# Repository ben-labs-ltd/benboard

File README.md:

# BenBoard

The highly customisable, open source, premium 42 key ergo mechanical keyboard

Show your interest at https://ben-labs.co.uk

## Features

- Reduced layout 42 key split keyboard
- Cherry MX hotswap compatable (any 3 or 5 pin)
- Fully wireless (BLE)
- Month-long battery life with the low power NRF52840
- Out of the box ZMK Support
- Supports [VIK](https://github.com/sadekbaroudi/vik) (on both sides!)
- Unibody case that has been verified to be CNC'able

## Contribution

[ ] TODO

## VIK Certification

| Category                 | Classification          | Response           |
| -----------------------  | ----------------------- | ------------------ |
| FPC connector            | Required                | :heavy_check_mark: |
| Breakout pins            | Recommended             | :x:                |
| Supplies: SPI            | Required                | :heavy_check_mark: |
| Supplies: I2C            | Required                | :heavy_check_mark: |
| I2C on main PCB          | Discouraged             | :x:                |
| I2C pull ups             | Informative             | :x:                |
| Supplies: RGB            | Required                | :heavy_check_mark: |
| Supplies: Extra GPIO 1   | Required                | :heavy_check_mark: (Analogue and Digital) |
| Supplies: Extra GPIO 2   | Required                | :heavy_check_mark: (Analogue and Digital) |

THIS IS A WORK IN PROGRESS, ANY FEATURES LISTED ARE PURELY IN PROGRESS

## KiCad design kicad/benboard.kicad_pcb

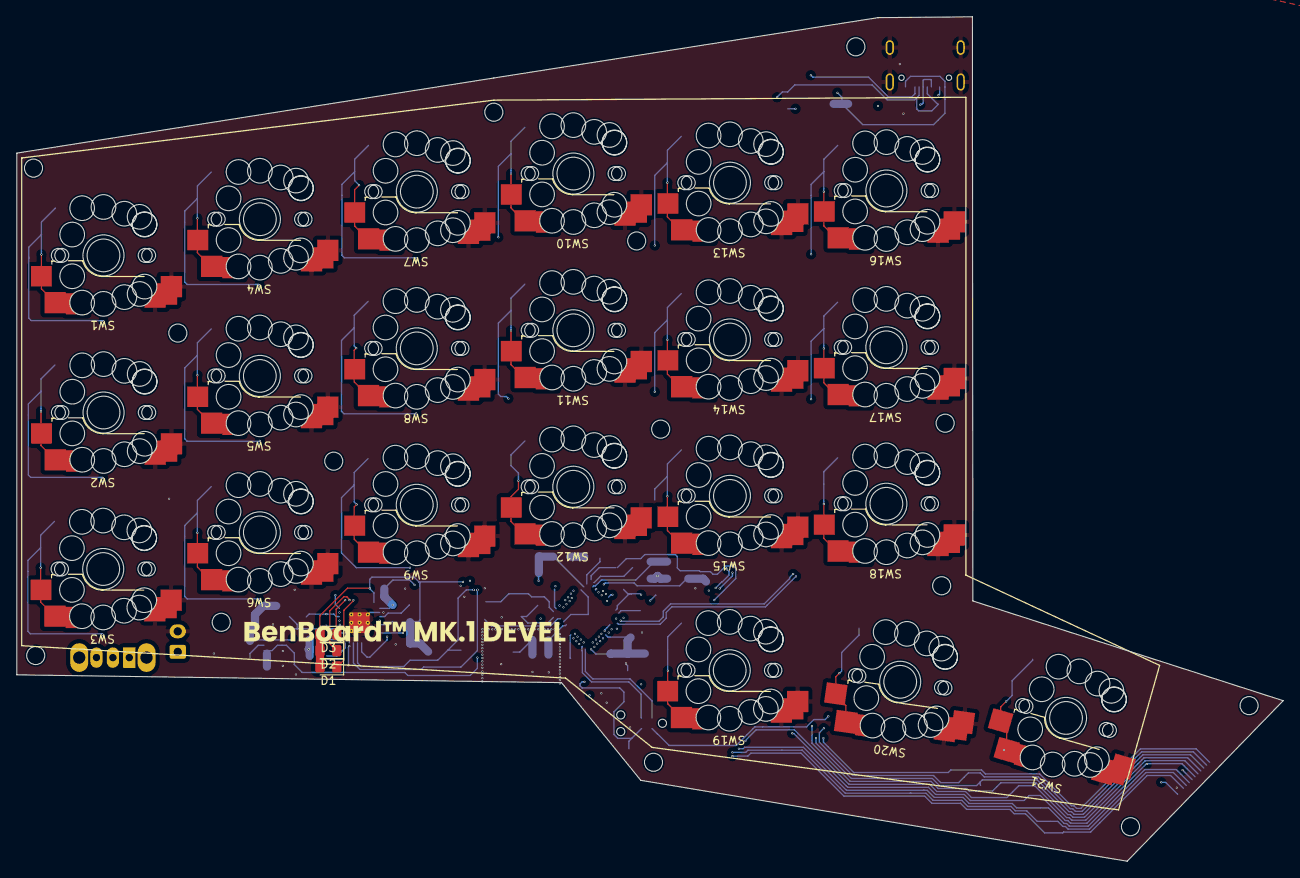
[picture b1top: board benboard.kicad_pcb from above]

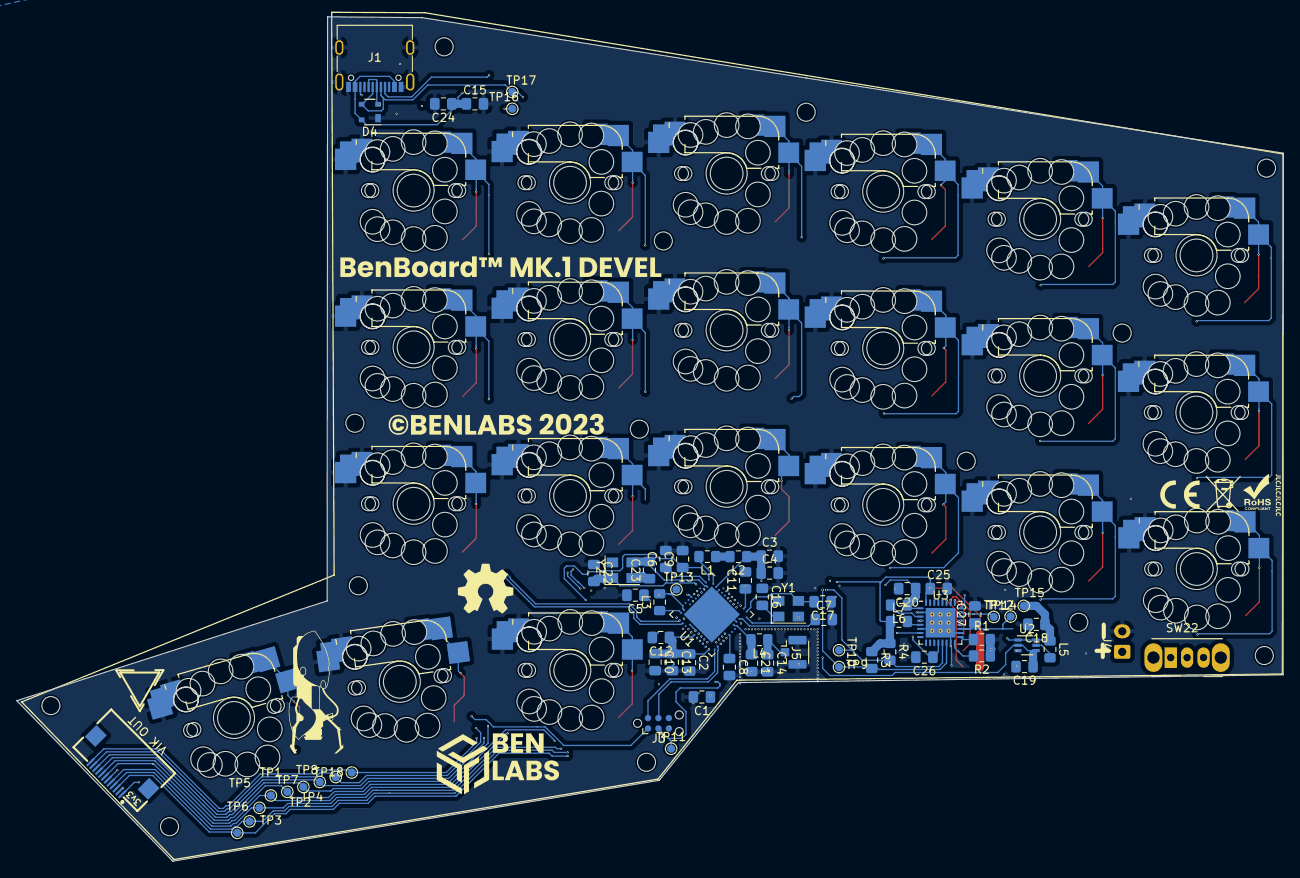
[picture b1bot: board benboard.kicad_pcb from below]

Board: 4 copper layers, 154.2 x 102.9 mm, 92 parts (67 on the bottom side), 70 nets.

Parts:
C1, C3, C13, C15: 1uF; C_0805_2012Metric_Pad1.18x1.45mm_HandSolder
C2, C5, C9: 4.7uF; C_0805_2012Metric_Pad1.18x1.45mm_HandSolder
C4: 47nF; C_0805_2012Metric_Pad1.18x1.45mm_HandSolder
C6, C10, C11, C12, C24, C26: 100nF; C_0805_2012Metric_Pad1.18x1.45mm_HandSolder
C7: 100pF; C_0805_2012Metric_Pad1.18x1.45mm_HandSolder
C8: 820pF; C_0805_2012Metric_Pad1.18x1.45mm_HandSolder
C14: 0.5pF; C_0805_2012Metric_Pad1.18x1.45mm_HandSolder
C16, C17, C22, C23: 12pF; C_0805_2012Metric_Pad1.18x1.45mm_HandSolder
C18, C19, C20, C25: 10uF; C_0805_2012Metric_Pad1.18x1.45mm_HandSolder
C21: 0.8pF; C_0805_2012Metric_Pad1.18x1.45mm_HandSolder
C27: 2.2uF; C_0805_2012Metric_Pad1.18x1.45mm_HandSolder
D1, D2, D3: LED; LED_0805_2012Metric_Pad1.15x1.40mm_HandSolder
D4: PRTR5V0U2X; SOT-143
J1: USB_C_Receptacle_USB2.0; USB_C_Receptacle_G-Switch_GT-USB-7010ASV
J2: vik-keyboard-connector-horizontal
J3: Conn_ARM_SWD_TagConnect_TC2030-NL; Tag-Connect_TC2030-IDC-NL_2x03_P1.27mm_Vertical
J4: Conn_01x02_Pin; JST_EH_B2B-EH-A_1x02_P2.50mm_Vertical
J5: Conn_Coaxial; U.FL_Hirose_U.FL-R-SMT-1_Vertical
L1, L3: 10uH; L_0805_2012Metric_Pad1.15x1.40mm_HandSolder
L2: 15nH; L_0805_2012Metric_Pad1.15x1.40mm_HandSolder
L4: 4.1nH; L_0805_2012Metric_Pad1.15x1.40mm_HandSolder
L5: 4.7uH; L_0805_2012Metric_Pad1.15x1.40mm_HandSolder
L6, L7: 2.2uH; L_0805_2012Metric_Pad1.15x1.40mm_HandSolder
R1, R3, R4: 47k; L_0805_2012Metric_Pad1.15x1.40mm_HandSolder
R2: 250k; L_0805_2012Metric_Pad1.15x1.40mm_HandSolder
SW1, SW2, SW3, SW4, SW5, SW6, SW7, SW8, SW9, SW10, SW11, SW12, SW13, SW14, SW15, SW16, SW17, SW18, SW19, SW20, SW21: SW_Push; gateron-ks27-choc-v1-mx-hotswap-reversible
SW22: SW_DPDT; SW_CuK_OS102011MA1QN1_SPDT_Angled
TP1, TP2, TP3, TP4, TP5, TP6, TP7, TP8, TP9, TP10, TP11, TP12, TP13, TP14, TP15, TP16, TP17, TP18: Probe; TestPoint_Pad_D1.0mm
U1: nRF52840; Nordic_AQFN-73-1EP_7x7mm_P0.5mm
U2: TPS61222DCK; Texas_R-PDSO-G6
U3: nPM1300-QEXX; QFN-32-1EP_5x5mm_P0.5mm_EP3.6x3.6mm_ThermalVias
Y1: 32MHz; Crystal_SMD_SeikoEpson_FA238V-4Pin_3.2x2.5mm
Y2: 32.768kHz; Crystal_SMD_SeikoEpson_FA238V-4Pin_3.2x2.5mm

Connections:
+3V3: C25.1, D1.2 (A), D2.2 (A), D3.2 (A), J2.1 (3V3), J3.1 (VCC), L7.1, R3.1, R4.1, U3.32 (VOUT2)
+5V: C19.1, J2.6 (5V), U2.2 (FB), U2.4 (VOUT)
CC1: J1.A5 (CC1), U3.23 (CC1)
CC2: J1.B5 (CC2), U3.24 (CC2)
D+: D4.2 (I/O1), J1.A6 (D+), J1.B6 (D+), TP16.1, U1.AD6 (D+)
D-: D4.3 (I/O2), J1.A7 (D-), J1.B7 (D-), TP17.1, U1.AD4 (D-)
GND: C1.2, C2.2, C3.2, C4.2, C5.2, C6.2, C7.2, C8.2, C9.2, C10.2, C11.2, C12.2, C13.2, C14.2, C15.2, C16.1, C17.1, C18.2, C19.2, C20.2, C21.2, C22.1, C23.1, C24.2, C25.2, C26.2, C27.2, D4.1 (GND), J1.A1 (GND), J1.A12 (GND), J1.B1 (GND), J1.B12 (GND), J1.S1 (SHIELD), J2.2 (GND), J3.5 (GND), J4.2, J5.2 (Ext), R1.2, R2.1, SW1.1, SW2.1, SW3.1, SW4.1, SW5.1, SW6.1, SW7.1, SW8.1, SW9.1, SW10.1, SW11.1, SW12.1, SW13.1, SW14.1, SW15.1, SW16.1, SW17.1, SW18.1, SW19.1, SW20.1, SW21.1, U1.B7 (VSS), U1.EP (VSS), U1.F23 (VSS_PA), U2.3 (GND), U3.2 (PVSS1), U3.6 (PVSS2), U3.15 (SHPHLD), U3.18 (NTC), U3.33 (AVSS), Y1.2, Y2.2
MISO: J2.11 (MISO), TP8.1, U1.A14 (P1.15)
MOSI: J2.8 (MOSI), TP7.1, U1.A20 (P1.10)
unnamed: D1.1 (K), U3.27 (LED2)
unnamed: D2.1 (K), U3.26 (LED1)
unnamed: D3.1 (K), U3.25 (LED0)
unnamed: J4.1, SW22.3 (C)
unnamed: C14.1, J5.1 (In), L4.1
unnamed: L1.1, L2.2
unnamed: C21.1, L4.2, U1.H23 (ANT)
unnamed: L1.2, U1.B3 (DCC)
unnamed: L3.1, U1.AB2 (DCCH)
unnamed: C6.1, U1.C1 (DEC1)
unnamed: C7.1, U1.D23 (DEC3)
unnamed: C3.1, C4.1, L2.1, U1.B5 (DEC4), U1.E24 (DEC6)
unnamed: C8.1, U1.N24 (DEC5)
unnamed: C5.1, U1.AC5 (DECUSB)
unnamed: C16.2, U1.B24 (XC1), Y1.1
unnamed: C17.2, U1.A23 (XC2), Y1.3
unnamed: C23.2, U1.D2 (XL1/P0.00), Y2.3
unnamed: C22.2, U1.F2 (XL2/P0.01), Y2.1
unnamed: L5.2, U2.5 (L)
unnamed: L6.2, U3.3 (SW1)
unnamed: L7.2, U3.5 (SW2)
unnamed: R1.1, U3.17 (VSET1)
unnamed: R2.2, U3.16 (VSET2)
RST: J3.3 (~RESET), TP11.1, U1.AC9 (P0.14), U1.AC11 (P0.16), U1.AC13 (P0.18/~RESET), U3.7 (GPIO0)
SCK: R3.2, TP9.1, U1.K2 (AIN3/P0.05), U3.14 (SCL)
SCLK: J2.12 (SCLK), TP18.1, U1.A10 (AIN5/P0.29)
SDA: R4.2, TP10.1, U1.J1 (AIN2/P0.04), U3.13 (SDA)
SPICS: J2.10 (SPI_CS), TP4.1, U1.A16 (P1.13)
SW1: SW1.2, U1.L1 (P0.06)
SW2: SW2.2, U1.AC15 (P0.19)
SW3: SW3.2, U1.AC21 (P0.25)
SW4: SW4.2, U1.AD10 (P0.15)
SW5: SW5.2, U1.P2 (P1.08)
SW6: SW6.2, U1.AC19 (P0.23)
SW7: SW7.2, U1.AD12 (P0.17)
SW8: SW8.2, U1.N1 (P0.08)
SW9: SW9.2, U1.AC17 (P0.21)
SW10: SW10.2, U1.AD16 (P0.20)
SW11: SW11.2, U1.AD22 (TRACEDATA0/P1.00)
SW12: SW12.2, U1.R24 (P1.06)
SW13: SW13.2, U1.AD18 (P0.22)
SW14: SW14.2, U1.W24 (P1.02)
SW15: SW15.2, U1.Y23 (P1.01)
SW16: SW16.2, U1.AD20 (P0.24)
SW17: SW17.2, U1.U24 (P1.04)
SW18: SW18.2, U1.H2 (P0.27)
SW19: SW19.2, U1.P23 (P1.07)
SW20: SW20.2, U1.T23 (P1.05)
SW21: SW21.2, U1.V23 (P1.03)
SWDC: J3.4 (SWCLK), U1.AA24 (SWDCLK)
SWDI: J3.2 (SWDIO), U1.AC24 (SWDIO)
VBAT: C27.1, SW22.2 (B), TP14.1, U3.19 (VBAT)
VBUS_IN: C15.1, C24.1, D4.4 (VCC), J1.A4 (VBUS), J1.A9 (VBUS), J1.B4 (VBUS), J1.B9 (VBUS), U3.21 (VBUS)
VBUS_MAIN: C1.1, TP12.1, U1.AD2 (VBUS), U3.22 (VBUSOUT)
VDD_NRF: C2.1, C9.1, C10.1, C11.1, C12.1, C13.1, C20.1, C26.1, L3.2, L6.1, TP13.1, U1.A22 (VDD), U1.AD14 (VDD), U1.AD23 (VDD), U1.B1 (VDD), U1.W1 (VDD), U1.Y2 (VDDH), U3.1 (VOUT1), U3.12 (VDDIO)
VIK_A0: J2.7 (GPIO_AD1), TP1.1, U1.A12 (AIN0/P0.02)
VIK_A1: J2.9 (GPIO_AD2), TP2.1, U1.B13 (AIN1/P0.03)
VIK_RGB: J2.5 (RGB_LED_OUT), TP3.1, U1.B15 (P1.14)
VIK_SCL: J2.4 (SCL), TP5.1, U1.B17 (P1.12)
VIK_SDA: J2.3 (SDA), TP6.1, U1.B19 (P1.11)
VSYS: C18.1, L5.1, TP15.1, U2.1 (VIN), U2.6 (EN), U3.4 (PVDD), U3.20 (VSYS)

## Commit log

2023-07-26 Ben Labs LTD. Now owns the BenBoard
2023-07-28 more cad files as well as readme
2023-07-31 add vik
2023-08-05 move
2023-08-09 add vik and SWD
2023-08-09 routes for some stuff
2023-08-09 VIK Compatible
2023-08-09 epic
2023-08-09 proper footprint
2023-08-17 minor changes, inc VIK compat
2023-08-17 this is so epic
2023-08-18 schematic basically done
2023-08-18 almost ready for prototype 0
2023-08-19 benboard v0.0 r0.1
2023-08-19 that's it now i SWEAR
2024-08-23 new revision
